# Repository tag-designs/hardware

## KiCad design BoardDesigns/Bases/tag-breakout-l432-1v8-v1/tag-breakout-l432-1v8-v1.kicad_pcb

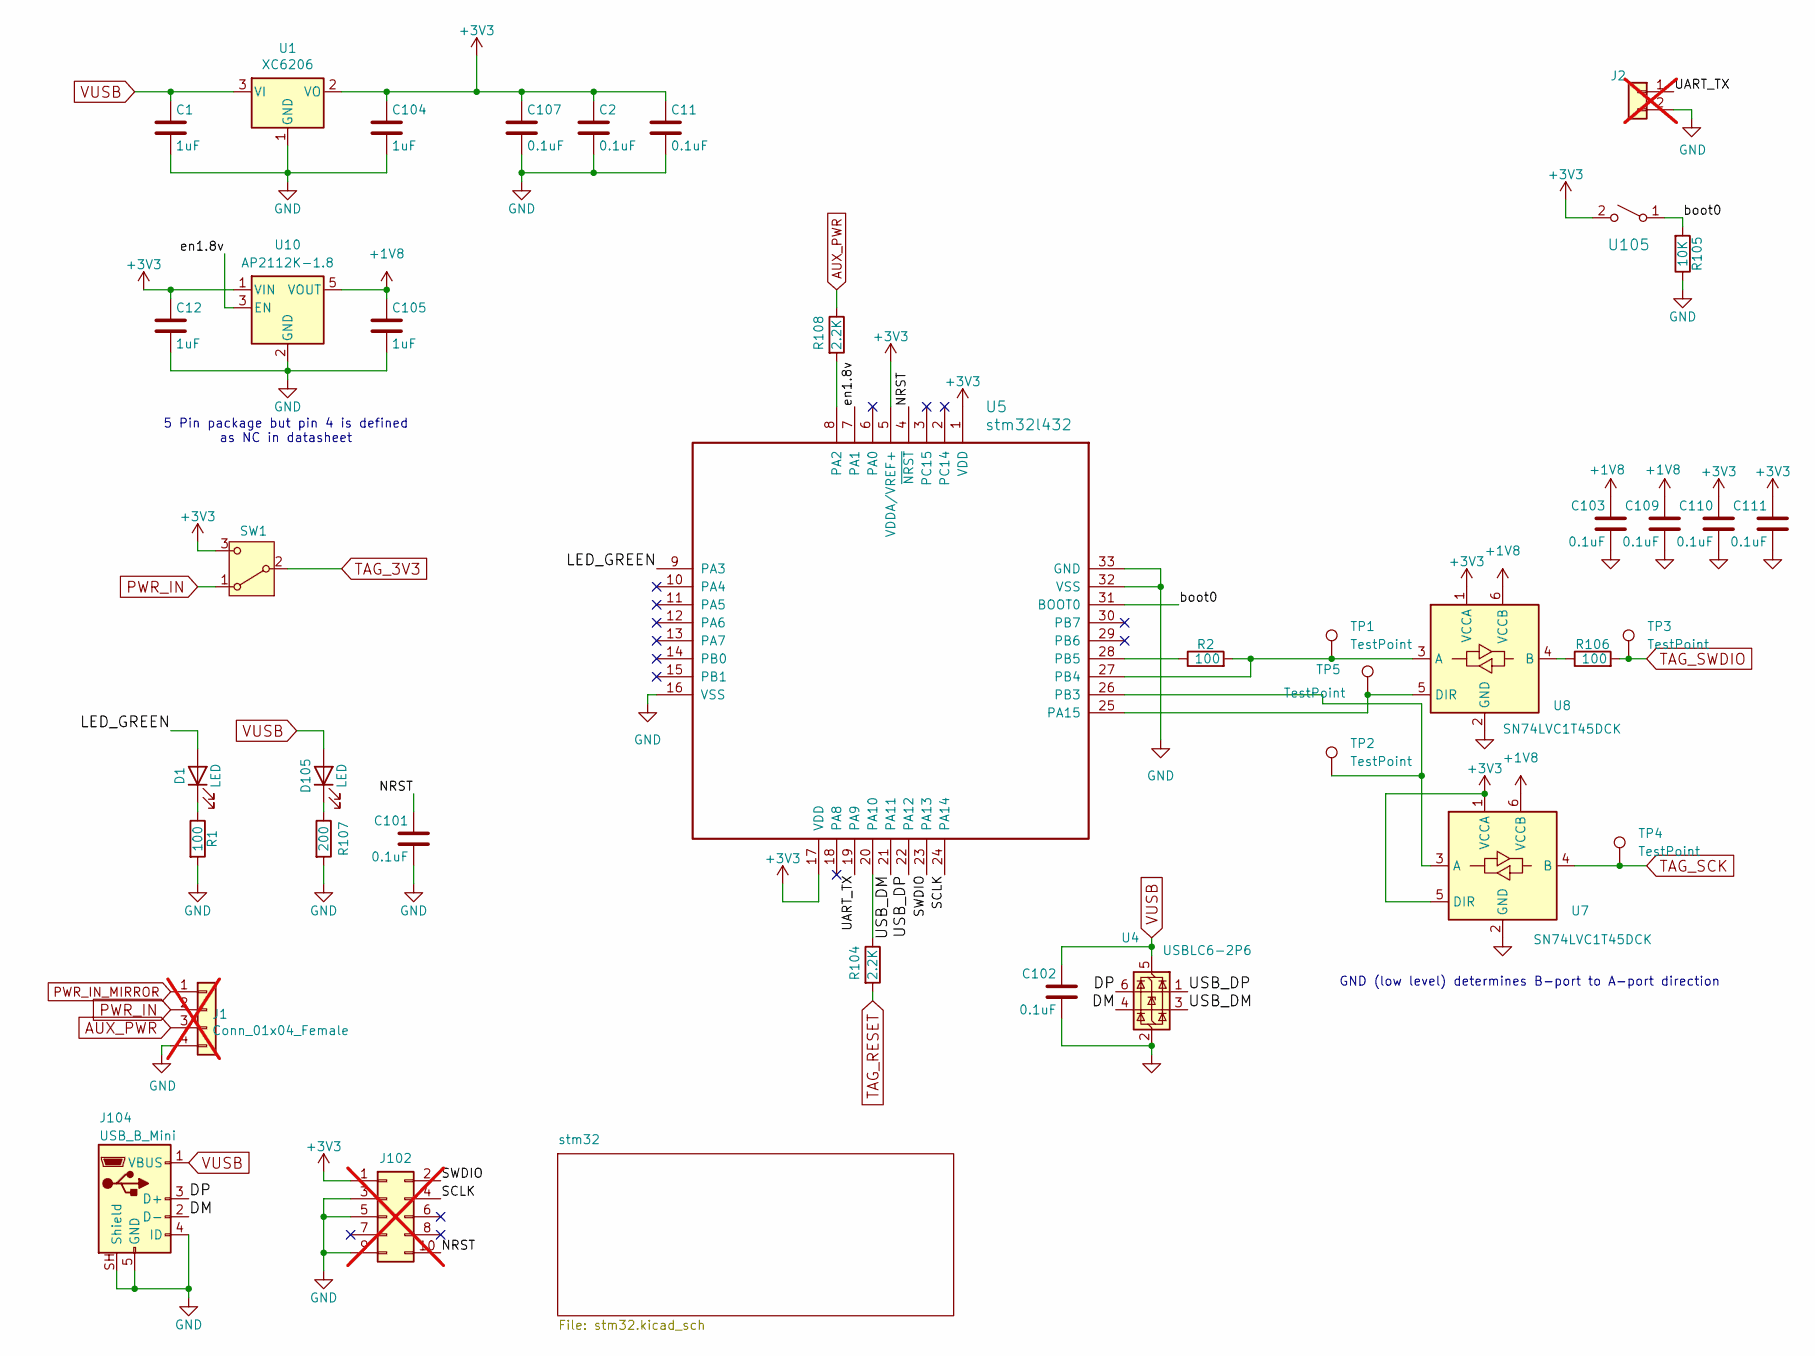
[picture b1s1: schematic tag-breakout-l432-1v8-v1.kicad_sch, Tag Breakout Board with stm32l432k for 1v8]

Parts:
C1, C12, C104, C105: 1uF; C_0402_1005Metric; MPN CL05A105KA5NQNC; LCSC C52923
C2, C11, C101, C102, C103, C107, C109, C110, C111: 0.1uF; C_0402_1005Metric; MPN CL05B104KO5NNNC; LCSC C1525
D1: LED; LED_0805_2012Metric; MPN KT-0805G; LCSC C2297
D105: LED; LED_0603_1608Metric; MPN KT-0603R; LCSC C2286
J1: Conn_01x04_Female; JST_XH_B04B-XH-AM_1x04_P2.50mm_Vertical; not fitted
J2: Conn_01x02_Male; PinHeader_1x02_P2.54mm_Vertical; not fitted
J102: Conn_02x05_Odd_Even; FTSH-105-01-F-D-K; not fitted
J104: USB_B_Mini; USB_Mini-B_Lumberg_2486_01_Horizontal; MPN MINI 5PTP; LCSC C2681563
R1, R2, R106: 100; R_0402_1005Metric; MPN 0402WGF1000TCE; LCSC C25076
R104, R108: 2.2K; R_0402_1005Metric; MPN 0402WGF2201TCE; LCSC C25879
R105: 10K; R_0402_1005Metric; MPN 0402WGF1002TCE; LCSC C25744
R107: 200; R_0402_1005Metric; MPN 0402WGF2000TCE; LCSC C25087
SW1: SW_SPDT; CJS-1200B_NDC; MPN CJS-1200B2; LCSC C35817163
TP1, TP2, TP3, TP4, TP5: TestPoint; TestPoint_Pad_D2.5mm
U1: XC6206; SOT-23-3; MPN XC6206P332MR-G; LCSC C5446
U4: USBLC6-2P6; SOT-666; MPN USBLC6-2P6; LCSC C15999
U5: stm32l432; UFQFPN-32-1EP_5x5mm_P0.5mm_EP3.5x3.5mm; MPN STM32L432KBU6TR; LCSC C2928224
U7, U8: SN74LVC1T45DCK; SOT-363_SC-70-6; MPN SN74LVC1T45DCKR; LCSC C9382
U10: AP2112K-1.8; SOT-23-5; MPN AP2112K-1.8TRG1(MS); LCSC C22365428
U105: Tactile Switch; SW_SPST_TS_1187; MPN TS-1187A-C-E-B; LCSC C318889

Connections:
+1V8: C103.1, C105.1, C109.1, U7.6 (VCCB), U8.6 (VCCB), U10.5 (VOUT)
+3V3: C2.1, C11.1, C12.1, C104.1, C107.1, C110.1, C111.1, J102.1, SW1.3 (C), U1.2 (VO), U5.1 (VDD), U5.5 (VDDA/VREF+), U5.17 (VDD), U7.1 (VCCA), U7.5 (DIR), U8.1 (VCCA), U10.1 (VIN), U105.2 (B)
/DM: J104.2 (D-), U4.4 (I/O2)
/DP: J104.3 (D+), U4.6 (I/O1)
/LED_GREEN: D1.2 (A), U5.9 (PA3)
/NRST: C101.1, J102.10, U5.4 (~NRST)
/SCLK: J102.4, U5.24 (PA14)
/SWDIO: J102.2, U5.23 (PA13)
/UART_TX: J2.1, U5.19 (PA9)
/USB_DM: U4.3 (I/O2), U5.21 (PA11)
/USB_DP: U4.1 (I/O1), U5.22 (PA12)
/boot0: R105.2, U5.31 (BOOT0), U105.1 (A)
/en1.8v: U5.7 (PA1), U10.3 (EN)
AUX_PWR: J1.3, R108.1
GND: C1.2, C2.2, C11.2, C12.2, C101.2, C102.2, C103.2, C104.2, C105.2, C107.2, C109.2, C110.2, C111.2, J1.4, J2.2, J102.3, J102.5, J102.9, J104.4 (ID), J104.5 (GND), J104.SH (Shield), R1.2, R105.1, R107.2, U1.1 (GND), U4.2 (GND), U5.16 (VSS), U5.32 (VSS), U5.33 (GND), U7.2 (GND), U8.2 (GND), U10.2 (GND); also elsewhere on the board
unnamed: D1.1 (K), R1.1
unnamed: D105.1 (K), R107.1
unnamed: R108.2, U5.8 (PA2)
unnamed: R104.1, U5.20 (PA10)
unnamed: TP5.1 (1_1), U5.25 (PA15), U8.5 (DIR)
unnamed: TP2.1 (1_1), U5.26 (PB3), U7.3 (A)
unnamed: R2.2, TP1.1 (1_1), U5.27 (PB4), U8.3 (A)
unnamed: R2.1, U5.28 (PB5)
unnamed: R106.1, U8.4 (B)
PWR_IN: J1.2, SW1.1 (A)
PWR_IN_MIRROR: J1.1
TAG_3V3: SW1.2 (B); also elsewhere on the board
TAG_RESET: R104.2; also elsewhere on the board
TAG_SCK: TP4.1 (1_1), U7.4 (B); also elsewhere on the board
TAG_SWDIO: R106.2, TP3.1 (1_1); also elsewhere on the board
VUSB: C1.1, C102.1, D105.2 (A), J104.1 (VBUS), U1.3 (VI), U4.5 (VBUS)

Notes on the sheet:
5 Pin package but pin 4 is defined as NC in datasheet
GND (low level) determines B-port to A-port direction

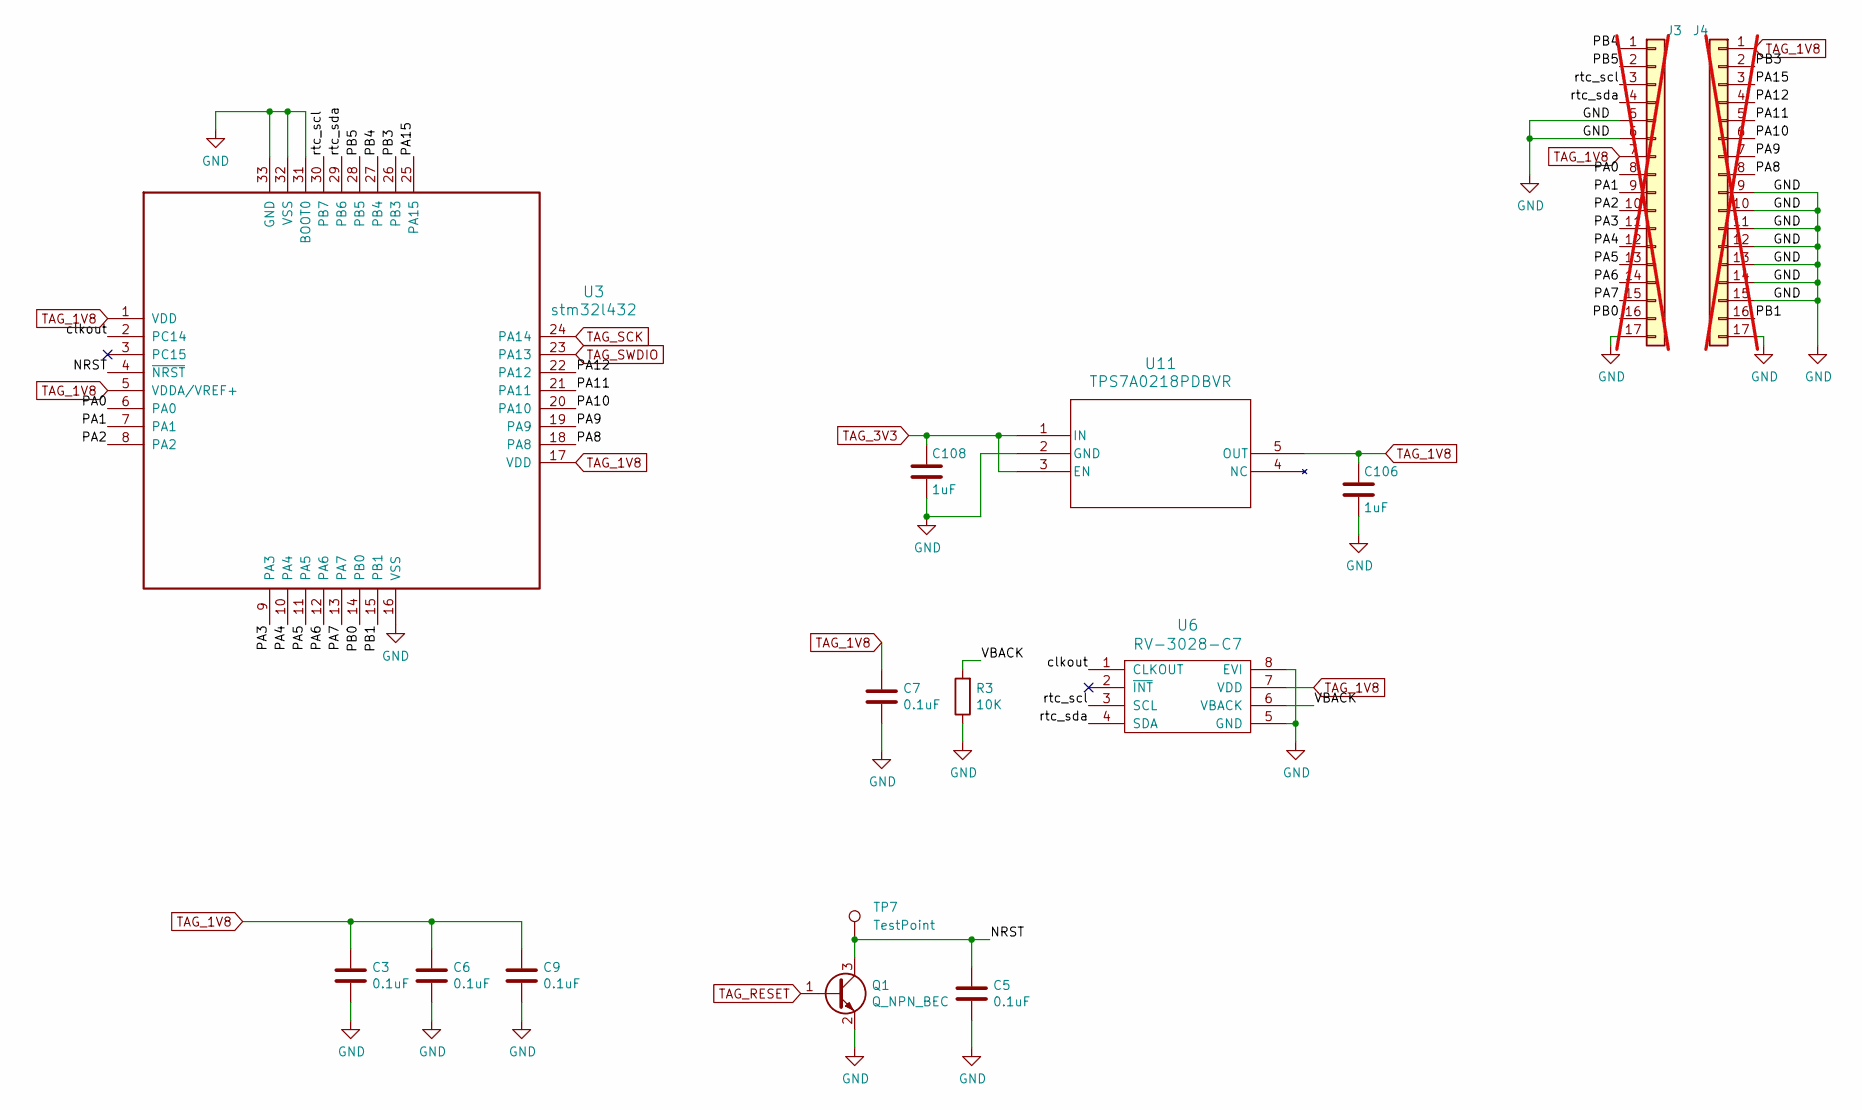
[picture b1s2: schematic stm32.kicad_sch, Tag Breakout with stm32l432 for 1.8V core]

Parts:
C3, C5, C6, C7, C9: 0.1uF; C_0402_1005Metric; MPN CL05B104KO5NNNC; LCSC C1525
C106, C108: 1uF; C_0402_1005Metric; MPN CL05A105KA5NQNC; LCSC C52923
J3, J4: Conn_01x17; PinHeader_1x17_P2.54mm_Vertical_Staggered; not fitted
Q1: Q_NPN_BEC; SOT-23; MPN BCX70H,215; LCSC C20527
R3: 10K; R_0402_1005Metric; MPN 0402WGF1002TCE; LCSC C25744
TP7: TestPoint; TestPoint_Pad_D2.5mm
U3: stm32l432; UFQFPN-32-1EP_5x5mm_P0.5mm_EP3.5x3.5mm; MPN STM32L432KBU6; LCSC C2928224
U6: RV-3028-C7; RV-8803-C7; MPN RV-3028-C7-32.768kHz-1ppm-TA-QC; LCSC C3019759
U11: TPS7A0218PDBVR; SOT-23-5; MPN TPS7A0218PDBVR; LCSC C3748843

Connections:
/stm32/NRST: C5.1, Q1.3 (C), TP7.1 (1_1), U3.4 (~NRST)
/stm32/PA0: J3.8, U3.6 (PA0)
/stm32/PA1: J3.9, U3.7 (PA1)
/stm32/PA2: J3.10, U3.8 (PA2)
/stm32/PA3: J3.11, U3.9 (PA3)
/stm32/PA4: J3.12, U3.10 (PA4)
/stm32/PA5: J3.13, U3.11 (PA5)
/stm32/PA6: J3.14, U3.12 (PA6)
/stm32/PA7: J3.15, U3.13 (PA7)
/stm32/PA8: J4.8, U3.18 (PA8)
/stm32/PA9: J4.7, U3.19 (PA9)
/stm32/PA10: J4.6, U3.20 (PA10)
/stm32/PA11: J4.5, U3.21 (PA11)
/stm32/PA12: J4.4, U3.22 (PA12)
/stm32/PA15: J4.3, U3.25 (PA15)
/stm32/PB0: J3.16, U3.14 (PB0)
/stm32/PB1: J4.16, U3.15 (PB1)
/stm32/PB3: J4.2, U3.26 (PB3)
/stm32/PB4: J3.1, U3.27 (PB4)
/stm32/PB5: J3.2, U3.28 (PB5)
/stm32/VBACK: R3.2, U6.6 (VBACK)
/stm32/clkout: U3.2 (PC14), U6.1 (CLKOUT)
/stm32/rtc_scl: J3.3, U3.30 (PB7), U6.3 (SCL)
/stm32/rtc_sda: J3.4, U3.29 (PB6), U6.4 (SDA)
GND: C3.2, C5.2, C6.2, C7.2, C9.2, C106.2, C108.2, J3.5, J3.6, J3.17, J4.9, J4.10, J4.11, J4.12, J4.13, J4.14, J4.15, J4.17, Q1.2 (E), R3.1, U3.16 (VSS), U3.31 (BOOT0), U3.32 (VSS), U3.33 (GND), U6.5 (GND), U6.8 (EVI), U11.2 (GND); also elsewhere on the board
TAG_1V8: C3.1, C6.1, C7.1, C9.1, C106.1, J3.7, J4.1, U3.1 (VDD), U3.5 (VDDA/VREF+), U3.17 (VDD), U6.7 (VDD), U11.5 (OUT)
TAG_3V3: C108.1, U11.1 (IN), U11.3 (EN); also elsewhere on the board
TAG_RESET: Q1.1 (B); also elsewhere on the board
TAG_SCK: U3.24 (PA14); also elsewhere on the board
TAG_SWDIO: U3.23 (PA13); also elsewhere on the board

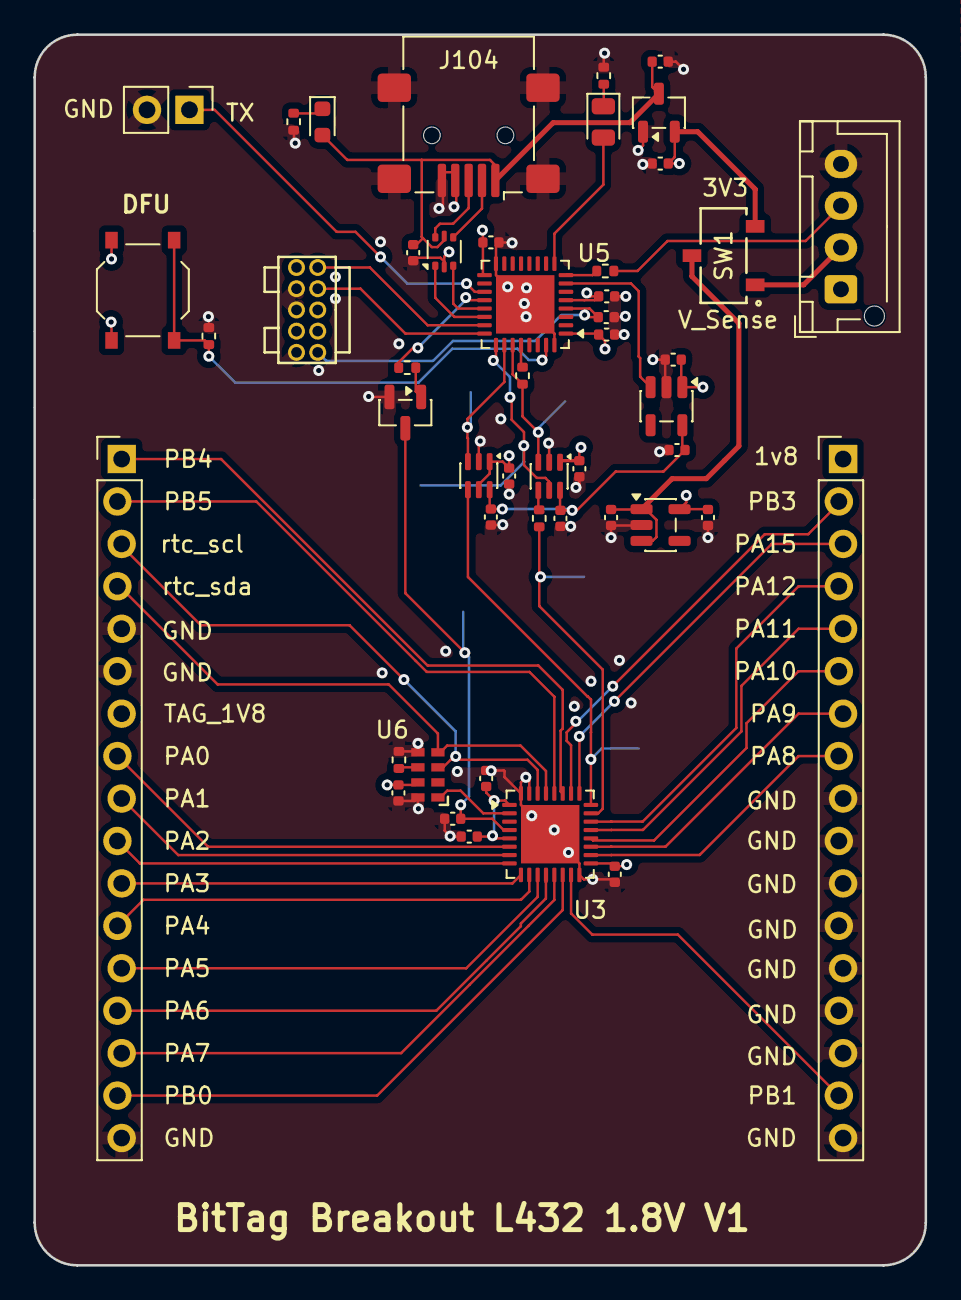
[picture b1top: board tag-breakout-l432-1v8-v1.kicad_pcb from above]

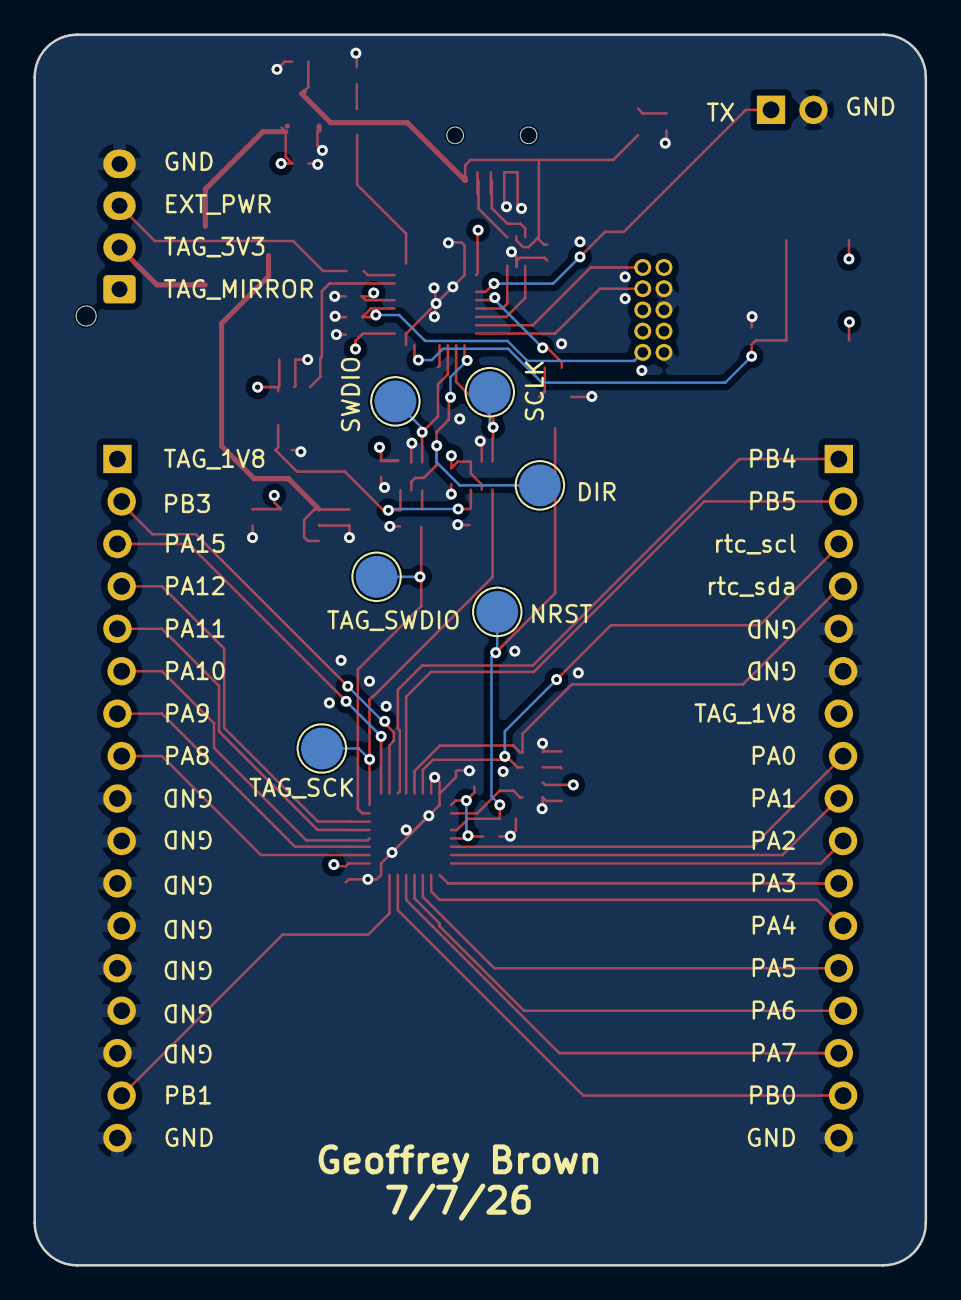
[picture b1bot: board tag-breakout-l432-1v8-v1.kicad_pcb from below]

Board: 4 copper layers, 53.3 x 73.7 mm, 54 parts (6 on the bottom side), 55 nets.

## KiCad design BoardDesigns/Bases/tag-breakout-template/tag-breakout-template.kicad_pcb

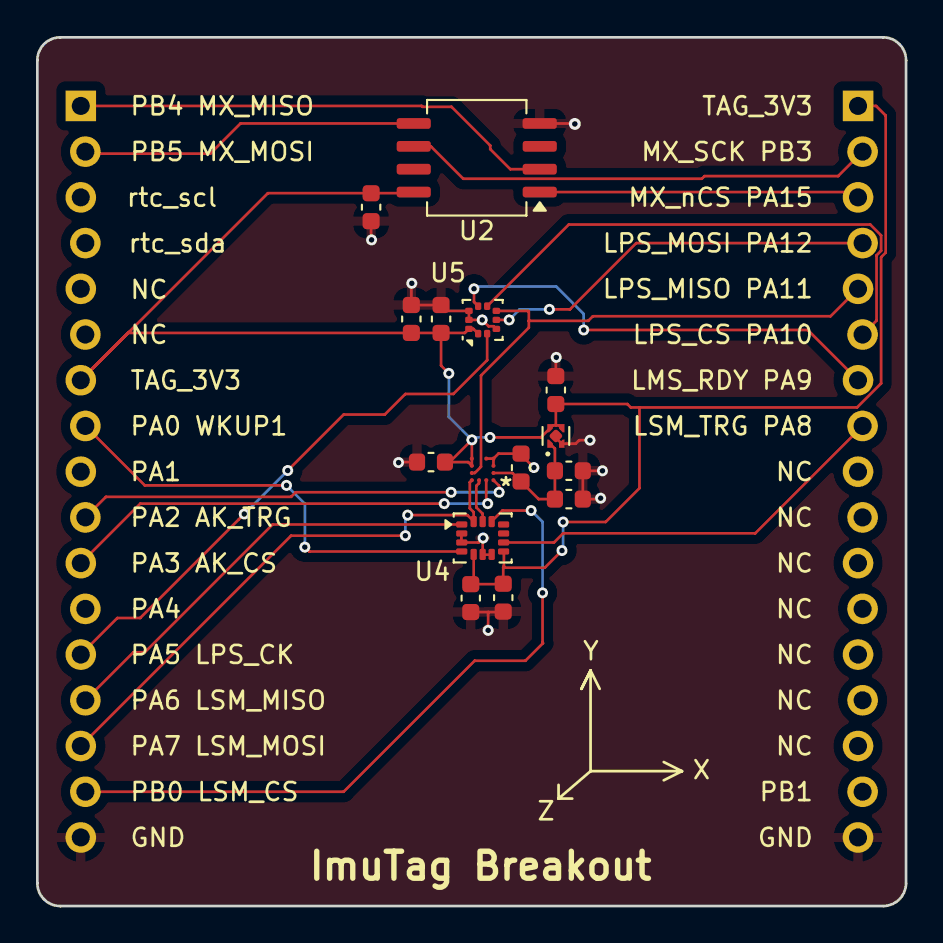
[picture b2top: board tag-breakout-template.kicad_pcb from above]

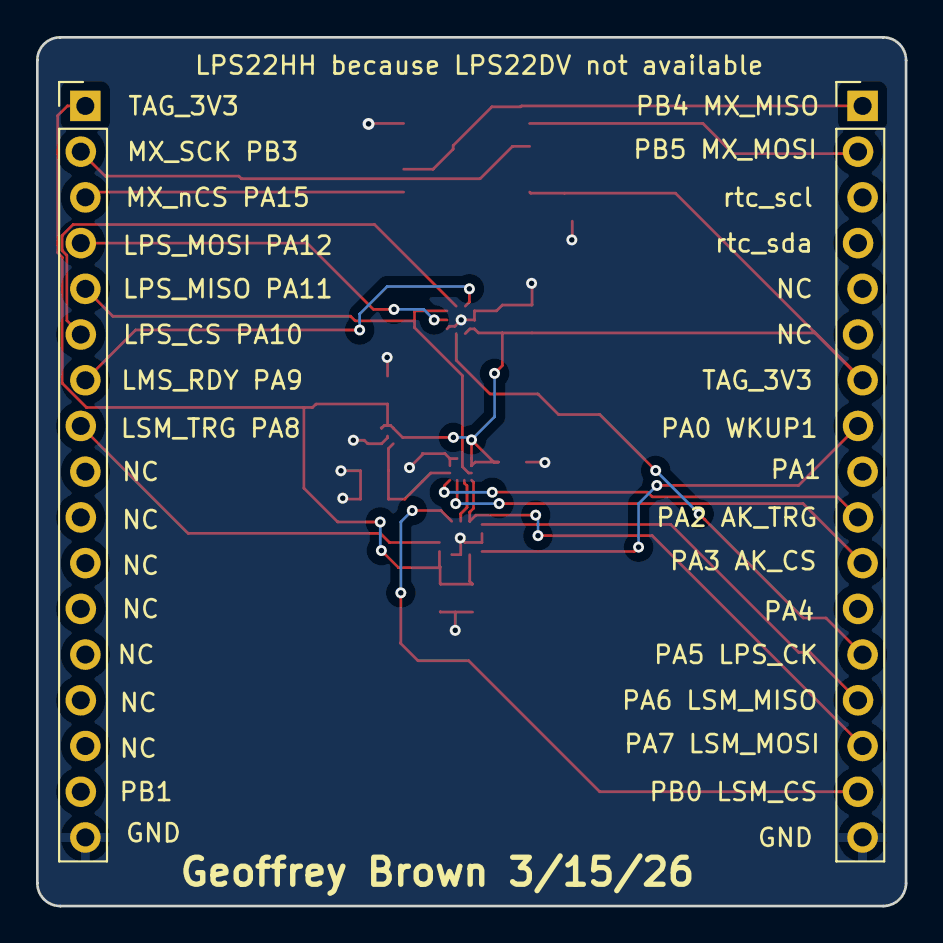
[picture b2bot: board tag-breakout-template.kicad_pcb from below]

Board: 2 copper layers, 48.3 x 48.3 mm, 17 parts (2 on the bottom side), 20 nets.

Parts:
C1, C2, C5, C6, C7, C8, C9, C10: 0.1uf; C_0603_1608Metric
C3, C4: 1uf; C_0603_1608Metric
J3, J4: Conn_01x17; PinHeader_1x17_P2.54mm_Vertical_Staggered
U1: TPS7A2018PDQN; Texas_X2SON-4_1x1mm_P0.65mm
U2: MX25L12835G; SOIC-8_5.3x6.2mm_P1.27mm
U3: AK09940A; AK09940a
U4: LSM6DSV16XTR; LGA-14_3x2.5mm_P0.5mm_LayoutBorder3x4y
U5: LPS22HH; ST_HLGA-10_2x2mm_P0.5mm_LayoutBorder3x2y

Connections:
+1V8: C4.1, C5.1, C8.1, U1.1 (OUT), U3.B1 (VDD)
+3.3V: C1.1, C2.1, C3.1, C6.1, C7.1, C9.1, C10.1, J3.7, J4.1, U1.3 (EN), U1.4 (IN), U2.8 (VCC), U3.C4 (VOD), U3.D4 (RSTN), U4.5 (VDD_IO), U4.8 (VDD), U5.1 (Vdd_IO), U5.10 (VDD)
/AK_CS: J3.11, U3.A2 (CSB)
/AK_TRG: J3.10, U3.A1 (DRDY/TRG)
/LPS_CK: J3.13, U5.2 (SCL)
/LPS_CS: J4.6, U5.6 (~CS)
/LPS_DRDY: J4.7, U5.7 (INT_DRDY)
/LPS_MISO: J4.5, U3.B4 (SO), U5.5 (SA0)
/LPS_MOSI: J4.4, U5.4 (SDA)
/LSM_CK: U3.A3 (SCL/SK), U4.13 (SCL)
/LSM_CS: J3.16, U4.12 (CS)
/LSM_MISO: J3.14, U4.1 (SDO/SA0)
/LSM_MOSI: J3.15, U3.A4 (SDA/SI), U4.14 (SDA)
/LSM_TRG: J4.8, U4.9 (INT2)
/MX_MISO: J3.1, U2.2 (SIO1)
/MX_MOSI: J3.2, U2.5 (SIO0)
/MX_SCK: J4.2, U2.6 (SCLK)
/MX_nCS: J4.3, U2.1 (nCS)
/WKUP1: J3.8, U4.4 (INT1)
GND: C1.2, C2.2, C3.2, C4.2, C5.2, C6.2, C7.2, C8.2, C9.2, C10.2, J3.17, J4.17, U1.2 (GND), U1.5 (Pad), U2.4 (GND), U3.C1 (VSS), U3.D1 (CAD0), U3.D2 (CAD1), U4.2 (SDX), U4.3 (SCX), U4.6 (GND), U4.7 (GND), U5.3 (GND), U5.8 (GND_IO), U5.9 (GND)

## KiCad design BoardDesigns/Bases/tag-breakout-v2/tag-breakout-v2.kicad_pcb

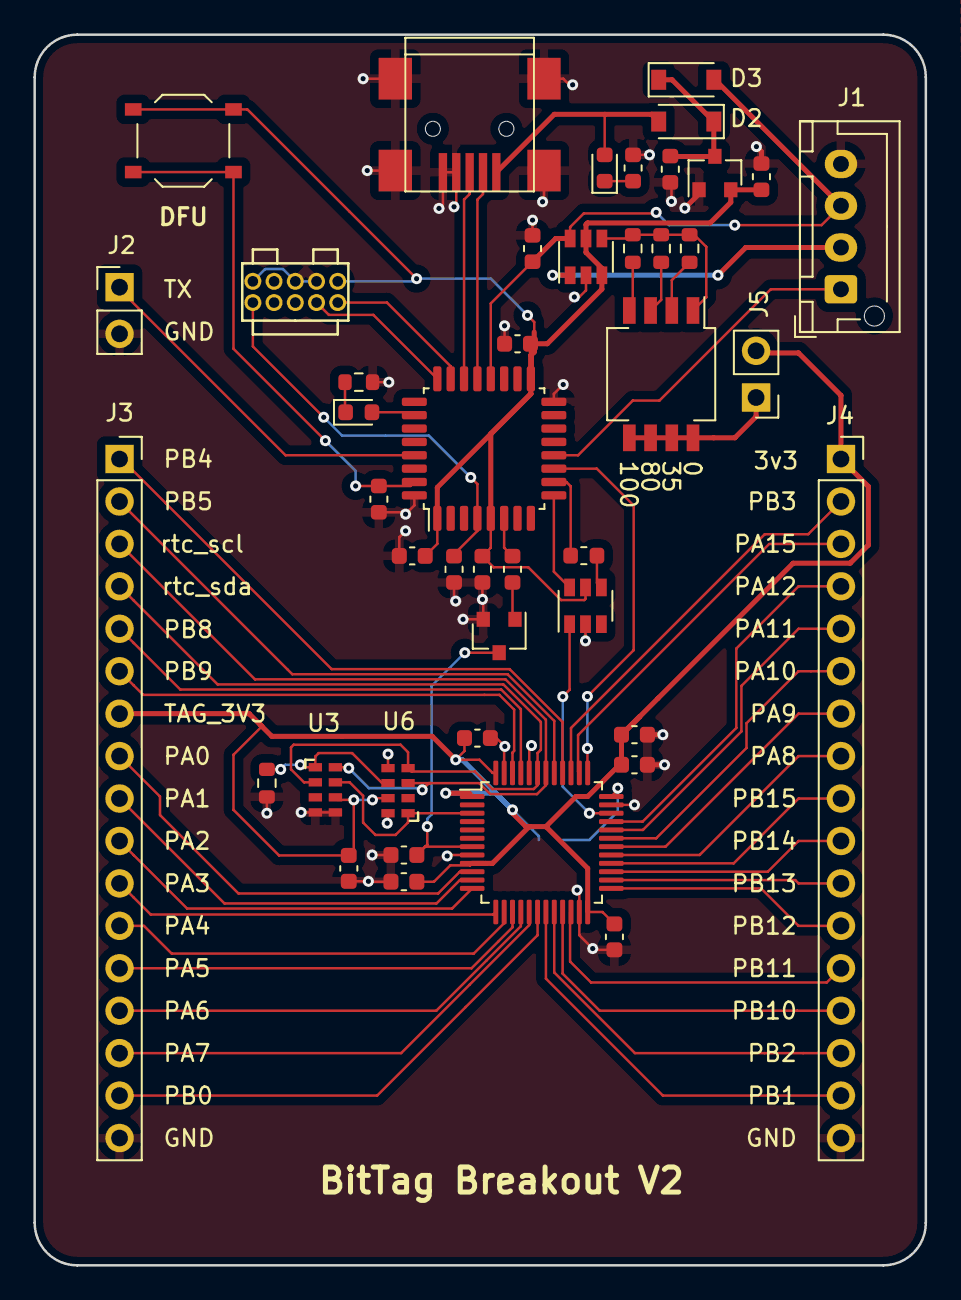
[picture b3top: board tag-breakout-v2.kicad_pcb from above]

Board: 2 copper layers, 53.3 x 73.7 mm, 45 parts (1 on the bottom side), 64 nets.

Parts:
C1, C104: 1uF; C_0603_1608Metric
C2, C3, C4, C5, C6, C7, C9, C11, C101, C107: 0.1uF; C_0603_1608Metric
C10: 4.7uF; C_0603_1608Metric
D1: LED-GREEN; LED_0603_1608Metric
D2, D3: D_Schottky; D_SOD-123
D105: LED-RED; LED_0603_1608Metric
J1: Conn_01x04_Female; JST_XH_B04B-XH-AM_1x04_P2.50mm_Vertical
J2, J5: Conn_01x02_Male; PinHeader_1x02_P2.54mm_Vertical
J3, J4: Conn_01x17; PinSocket_1x17_P2.54mm_Vertical
J102: Conn_02x05_Odd_Even; FTSH-105-01-F-D-K
J104: USB_B_Mini; USB_Mini-B
JP1: SolderJumper_2_Open; SolderJumper-2_P1.3mm_Open_TrianglePad1.0x1.5mm
Q1: Q_NPN_BEC; SOT-23
R1, R107: 620; R_0603_1608Metric
R2: 36; R_0603_1608Metric
R3, R105: 10K; R_0603_1608Metric
R4, R104: 2.2K; R_0603_1608Metric
R5: 82; R_0603_1608Metric
R6, R106: 100; R_0603_1608Metric
SW1: SW_DIP_x04; SW_DIP_SPSTx04_Slide_Copal_CHS-04B_W7.62mm_P1.27mm
U1: XC6206; SOT-23
U2, U4: TS5A3159ADBVR; SOT-23-6
U3: RV-3032-C7; RV-8803-C7
U6: RV-3028-C7; RV-8803-C7
U7: STM32L431CCTx; LQFP-48_7x7mm_P0.5mm
U101: STM32F042K6Tx; LQFP-32_7x7mm_P0.8mm
U105: Tactile Switch; SW_SPST_TS_1187

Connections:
+3V3: C2.1, C11.1, C104.1, C107.1, J102.1, U1.2, U2.5, U4.3, U4.5, U101.1, U101.5, U101.17, U105.2
/LED_GREEN: D1.2, U101.26
/NRST: C101.1, J102.10, U101.4
/SCLK: J102.4, U101.24
/SWDIO: J102.2, U101.23
/UART_TX: J2.1, U101.29
/USB_DM: J104.2, U101.21
/USB_DP: J104.3, U101.22
/boot0: R105.2, U101.31, U105.1
/stm32/NRST: C5.1, Q1.3, U7.7
/stm32/PA0: J3.8, U7.10
/stm32/PA1: J3.9, U7.11
/stm32/PA2: J3.10, U7.12
/stm32/PA3: J3.11, U7.13
/stm32/PA4: J3.12, U7.14
/stm32/PA5: J3.13, U7.15
/stm32/PA6: J3.14, U7.16
/stm32/PA7: J3.15, U7.17
/stm32/PA8: J4.8, U7.29
/stm32/PA9: J4.7, U7.30
/stm32/PA10: J4.6, U7.31
/stm32/PA11: J4.5, U7.32
/stm32/PA12: J4.4, U7.33
/stm32/PA15: J4.3, U7.38
/stm32/PB0: J3.16, U7.18
/stm32/PB1: J4.16, U7.19
/stm32/PB2: J4.15, U7.20
/stm32/PB3: J4.2, U7.39
/stm32/PB4: J3.1, U7.40
/stm32/PB5: J3.2, U7.41
/stm32/PB8: J3.5, U7.45
/stm32/PB9: J3.6, U7.46
/stm32/PB10: J4.14, U7.21
/stm32/PB11: J4.13, U7.22
/stm32/PB12: J4.12, U7.25
/stm32/PB13: J4.11, U7.26
/stm32/PB14: J4.10, U7.27
/stm32/PB15: J4.9, U7.28
/stm32/TAG_PWR: C3.1, C4.1, C6.1, C7.1, C9.1, C10.1, J3.7, J4.1, J5.2, JP1.1, U3.6, U6.7, U7.1, U7.9, U7.24, U7.48
/stm32/VBACK: R3.2, U3.1, U6.6
/stm32/clkout: U3.7, U6.1, U7.3
/stm32/rtc_scl: J3.3, U3.8, U6.3, U7.42
/stm32/rtc_sda: J3.4, U3.2, U6.4, U7.43
EXT_PWR: D3.2, J1.3, R4.1, U4.6, U101.20
GND: C1.2, C2.2, C3.2, C4.2, C5.2, C6.2, C7.2, C9.2, C10.2, C11.2, C101.2, C104.2, C107.2, J1.4, J2.2, J3.17, J4.17, J102.3, J102.5, J102.9, J104.4, J104.5, J104.6, Q1.2, R1.2, R3.1, R4.2, R105.1, R107.2, U1.1, U2.2, U3.4, U3.5, U4.2, U6.5, U6.8, U7.8, U7.23, U7.35, U7.44, U7.47, U101.16, U101.32
unnamed: C1.1, D2.1, D3.1, U1.3
unnamed: D1.1, R1.1
unnamed: D105.1, R107.1
unnamed: JP1.2, U7.36
unnamed: R2.1, SW1.2
unnamed: R2.2, R5.2, R6.2, SW1.1, U4.4
unnamed: R5.1, SW1.3
unnamed: R6.1, SW1.4
unnamed: R104.2, U101.6
unnamed: R106.1, U101.10
unnamed: R106.2, U2.4
unnamed: U2.6, U101.9
PWR_IN: J1.2, U4.1
PWR_IN_MIRROR: J1.1, U101.12
TAG_3V3: J5.1, SW1.5, SW1.6, SW1.7, SW1.8
TAG_RESET: Q1.1, R104.1
TAG_SCK: U7.37, U101.11
TAG_SWDIO: U2.1, U7.34
VUSB: D2.2, D105.2, J104.1
